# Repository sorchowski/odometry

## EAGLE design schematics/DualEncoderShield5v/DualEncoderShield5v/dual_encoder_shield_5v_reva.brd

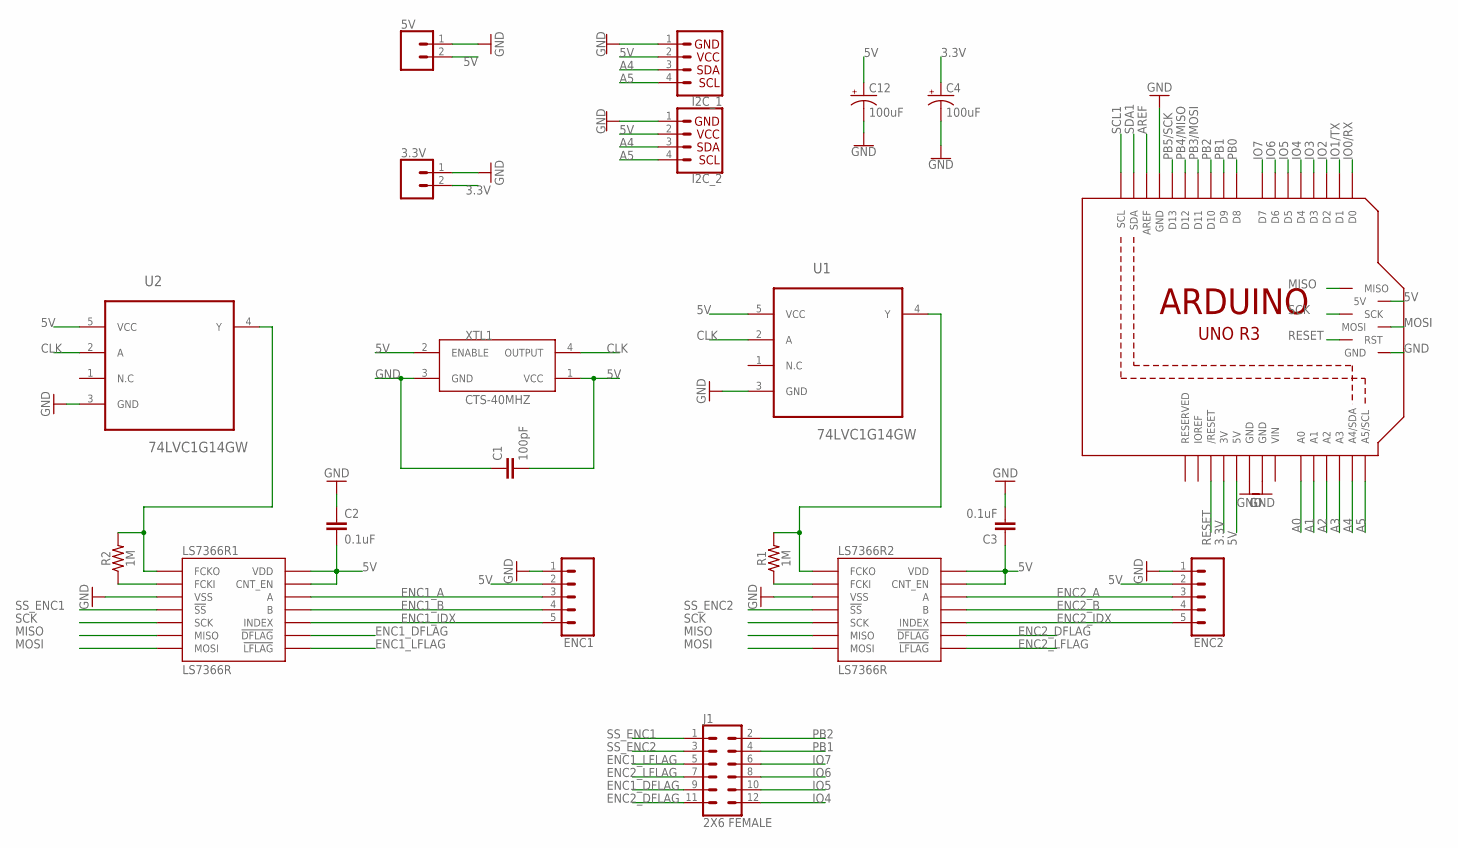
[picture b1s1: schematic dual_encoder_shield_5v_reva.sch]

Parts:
3.3V, 5V: CONN_02-JST-2MM-SMT; JST-2-SMD
C1: 100pF; 0603
C2, C3: 0.1uF; 0603
C4, C12: 100uF; PANASONIC_D
ENC1, ENC2: CONN_05; 1X05
I2C_1, I2C_2: QWIIC_CONNECTORJS-1MM; JST04_1MM_RA
J1: 2X6 FEMALE; 2X6
LS7366R1, LS7366R2: LS7366R; SOIC14
M1: ARDUINO_R3_ICSP; ARDUINOR3_ICSP
R1, R2: 1M; 0603
U1, U2: 74LVC1G14GW; SOT65P210X110-5N
XTL1: CTS-40MHZ; SOIC254P1016X440-4N

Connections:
3.3V: 3.3V.2 (1), C4.+, M1.3V
5V: 5V.2 (1), C1.2, C2.2, C3.1, C12.+, ENC1.2, ENC2.2, I2C_1.2, I2C_2.2, LS7366R1.13 (CNT_EN), LS7366R1.14 (VDD), LS7366R2.13 (CNT_EN), LS7366R2.14 (VDD), M1.5V, M1.5V_ICSP (5V), U1.5 (VCC), U2.5 (VCC), XTL1.1 (VCC), XTL1.2 (ENABLE)
A0: M1.A0
A1: M1.A1
A2: M1.A2
A3: M1.A3
A4: I2C_1.3, I2C_2.3, M1.A4 (A4/SDA)
A5: I2C_1.4, I2C_2.4, M1.A5 (A5/SCL)
AREF: M1.AREF
CLK: U1.2 (A), U2.2 (A), XTL1.4 (OUTPUT)
ENC1_A: ENC1.3, LS7366R1.12 (A)
ENC1_B: ENC1.4, LS7366R1.11 (B)
ENC1_DFLAG: J1.9, LS7366R1.9 (!DFLAG)
ENC1_IDX: ENC1.5, LS7366R1.10 (INDEX)
ENC1_LFLAG: J1.5, LS7366R1.8 (!LFLAG)
ENC2_A: ENC2.3, LS7366R2.12 (A)
ENC2_B: ENC2.4, LS7366R2.11 (B)
ENC2_DFLAG: J1.11, LS7366R2.9 (!DFLAG)
ENC2_IDX: ENC2.5, LS7366R2.10 (INDEX)
ENC2_LFLAG: J1.7, LS7366R2.8 (!LFLAG)
GND: 3.3V.1 (2), 5V.1 (2), C1.1, C2.1, C3.2, C4.-, C12.-, ENC1.1, ENC2.1, I2C_1.1, I2C_2.1, LS7366R1.3 (VSS), LS7366R2.3 (VSS), M1.GND, M1.GND@1 (GND), M1.GND@2 (GND), M1.GND@3 (GND), U1.3 (GND), U2.3 (GND), XTL1.3 (GND)
IO0/RX: M1.D0
IO1/TX: M1.D1
IO2: M1.D2
IO3: M1.D3
IO4: J1.12, M1.D4
IO5: J1.10, M1.D5
IO6: J1.8, M1.D6
IO7: J1.6, M1.D7
MISO: LS7366R1.6 (MISO), LS7366R2.6 (MISO), M1.MISO
MOSI: LS7366R1.7 (MOSI), LS7366R2.7 (MOSI), M1.MOSI
unnamed: LS7366R1.2 (FCKI), R2.1
unnamed: LS7366R2.1 (FCKO), R1.2, U1.4 (Y)
unnamed: LS7366R2.2 (FCKI), R1.1
unnamed: LS7366R1.1 (FCKO), R2.2, U2.4 (Y)
PB0: M1.D8
PB1: J1.4, M1.D9
PB2: J1.2, M1.D10
PB3/MOSI: M1.D11
PB4/MISO: M1.D12
PB5/SCK: M1.D13
RESET: M1.RESET (/RESET), M1.RESET_ICSP (RST)
SCK: LS7366R1.5 (SCK), LS7366R2.5 (SCK), M1.SCK
SCL1: M1.SCL
SDA1: M1.SDA
SS_ENC1: J1.1, LS7366R1.4 (!SS)
SS_ENC2: J1.3, LS7366R2.4 (!SS)
VIN: M1.VIN

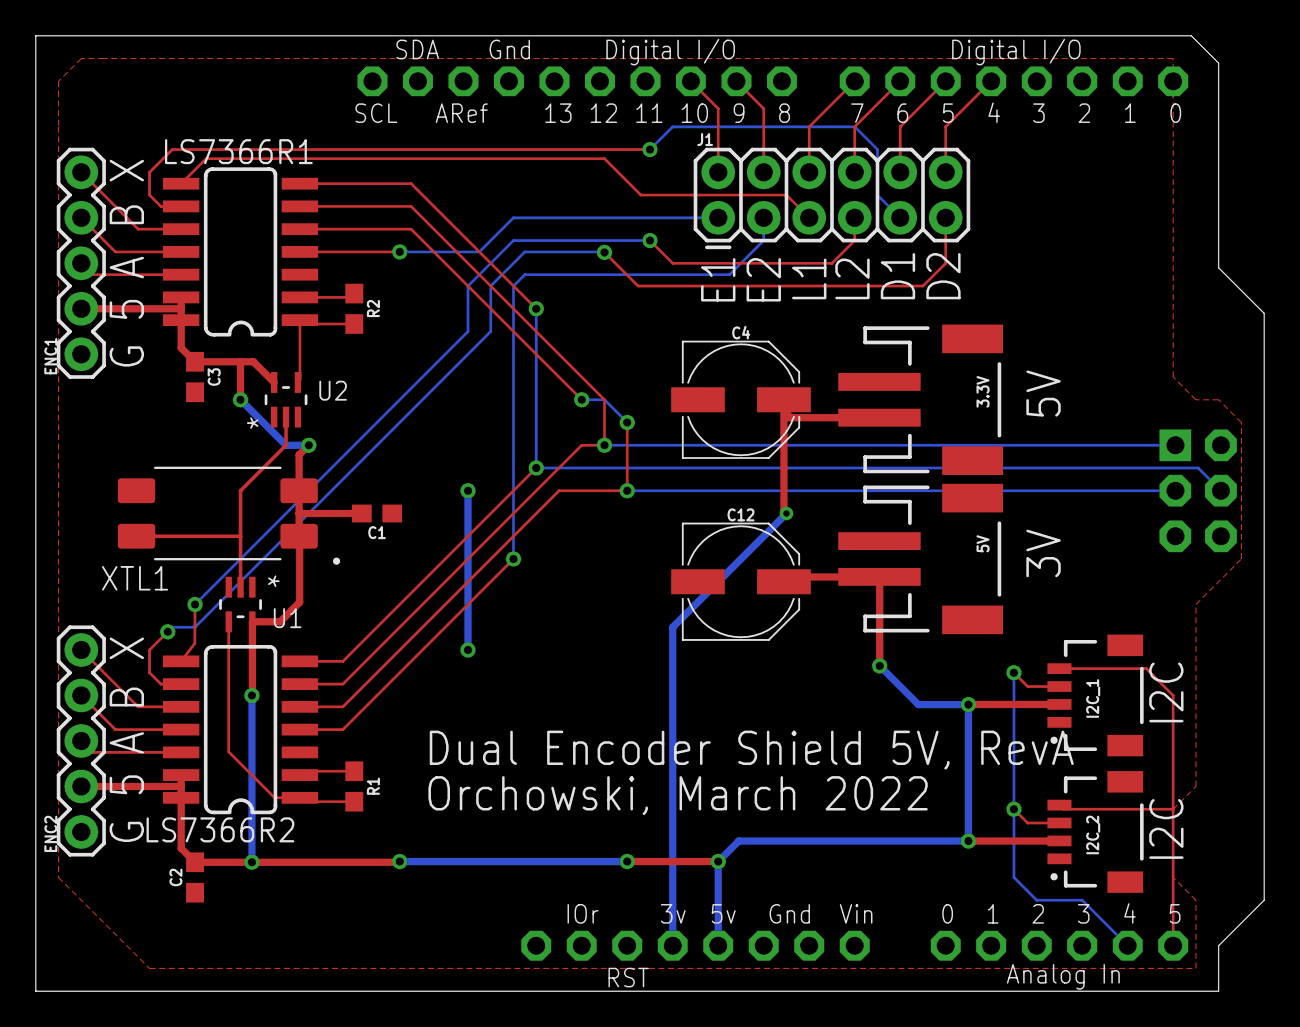
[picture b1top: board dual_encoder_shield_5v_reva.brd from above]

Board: 2 copper layers, 68.6 x 53.3 mm, 20 parts (0 on the bottom side), 32 nets.

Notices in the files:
parts and their libraries:
SparkFun-Connectors: Licensing: Creative Commons ShareAlike 4.0 International - https://creativecommons.org/licenses/by-sa/4.0
SparkFun: Licensing: CC v3.0 Share-Alike You are welcome to use this library for commercial purposes.
